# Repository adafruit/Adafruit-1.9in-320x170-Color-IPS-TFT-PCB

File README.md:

## Adafruit Adafruit 1.9" 320x170 Color IPS TFT Display - ST7789 PCB

<a href="http://www.adafruit.com/products/5394"><br/>
Click here to purchase one from the Adafruit shop</a>

PCB files for the Adafruit Adafruit 1.9" 320x170 Color IPS TFT Display - ST7789. 

Format is EagleCAD schematic and board layout
* https://www.adafruit.com/product/5394

### Description

This lovely little display breakout is the best way to add a small, colorful, and very bright display to any project. Since the display uses 4-wire SPI to communicate and has its own pixel-addressable frame buffer, it can be used with every kind of microcontroller. Even a very small one with low memory and few pins available! The 1.9" display has 320x170 16-bit full-color pixels and is an **IPS** display, so the color looks great up to 80 degrees off-axis in any direction. The TFT driver (ST7789) is very similar to the popular ST7735, and our Arduino library supports it well.

The breakout has the TFT display soldered on (it uses a delicate flex-circuit connector) as well as an ultra-low-dropout 3.3V regulator, auto-reset circuitry, and a 3/5V level shifter so you can use it with 3.3V or 5V power and logic. We also had a little extra space, so we placed a microSD card holder so you can easily load full color bitmaps from a FAT16/FAT32 formatted microSD card. The microSD card is not included, [but you can pick one up here](https://www.adafruit.com/product/5251).

Of course, we wouldn't just leave you with a datasheet and a "good luck!" - [we've written a full open-source graphics Arduino library that can draw pixels, lines, rectangles, circles, text, and bitmaps as well as example code](https://github.com/adafruit/Adafruit-ST7735-Library). The code is written for Arduino but can be easily ported to your favorite microcontroller! Wiring is easy, we strongly encourage using the hardware SPI pins of your Arduino as software SPI is noticeably slower when dealing with this size display. [For Raspberry Pi or other Single Board Computer Python users, we have a user-space Pillow-compatible library](https://github.com/adafruit/Adafruit_CircuitPython_RGB_Display). For [CircuitPython there's a displayio driver for native support](https://github.com/adafruit/Adafruit_CircuitPython_ST7789).

This display breakout also features an 18-pin "EYE SPI" standard FPC connector with flip-top connector. You can use an 18-pin 0.5mm pitch FPC cable to connect to all the GPIO pins, for when you want to skip the soldering.

**Please note!** This display is designed original for smartwatches and similar, where there's a glass over the screen. Without something gently holding the screen down, the backlight can eventually peel away from the TFT. (It's not destructive but it's unattractive) You can prevent this by, ideally, adding a plastic or glass cover/overlay. If using bare, try dabbing a touch of E6000 or similar craft glue on the thin side edges, or using a thin piece of tape to keep the front TFT attached to the backlight.

### License

Adafruit invests time and resources providing this open source design, please support Adafruit and open-source hardware by purchasing products from [Adafruit](https://www.adafruit.com)!

Designed by Limor Fried/Ladyada for Adafruit Industries.

Creative Commons Attribution/Share-Alike, all text above must be included in any redistribution. 
See license.txt for additional details.

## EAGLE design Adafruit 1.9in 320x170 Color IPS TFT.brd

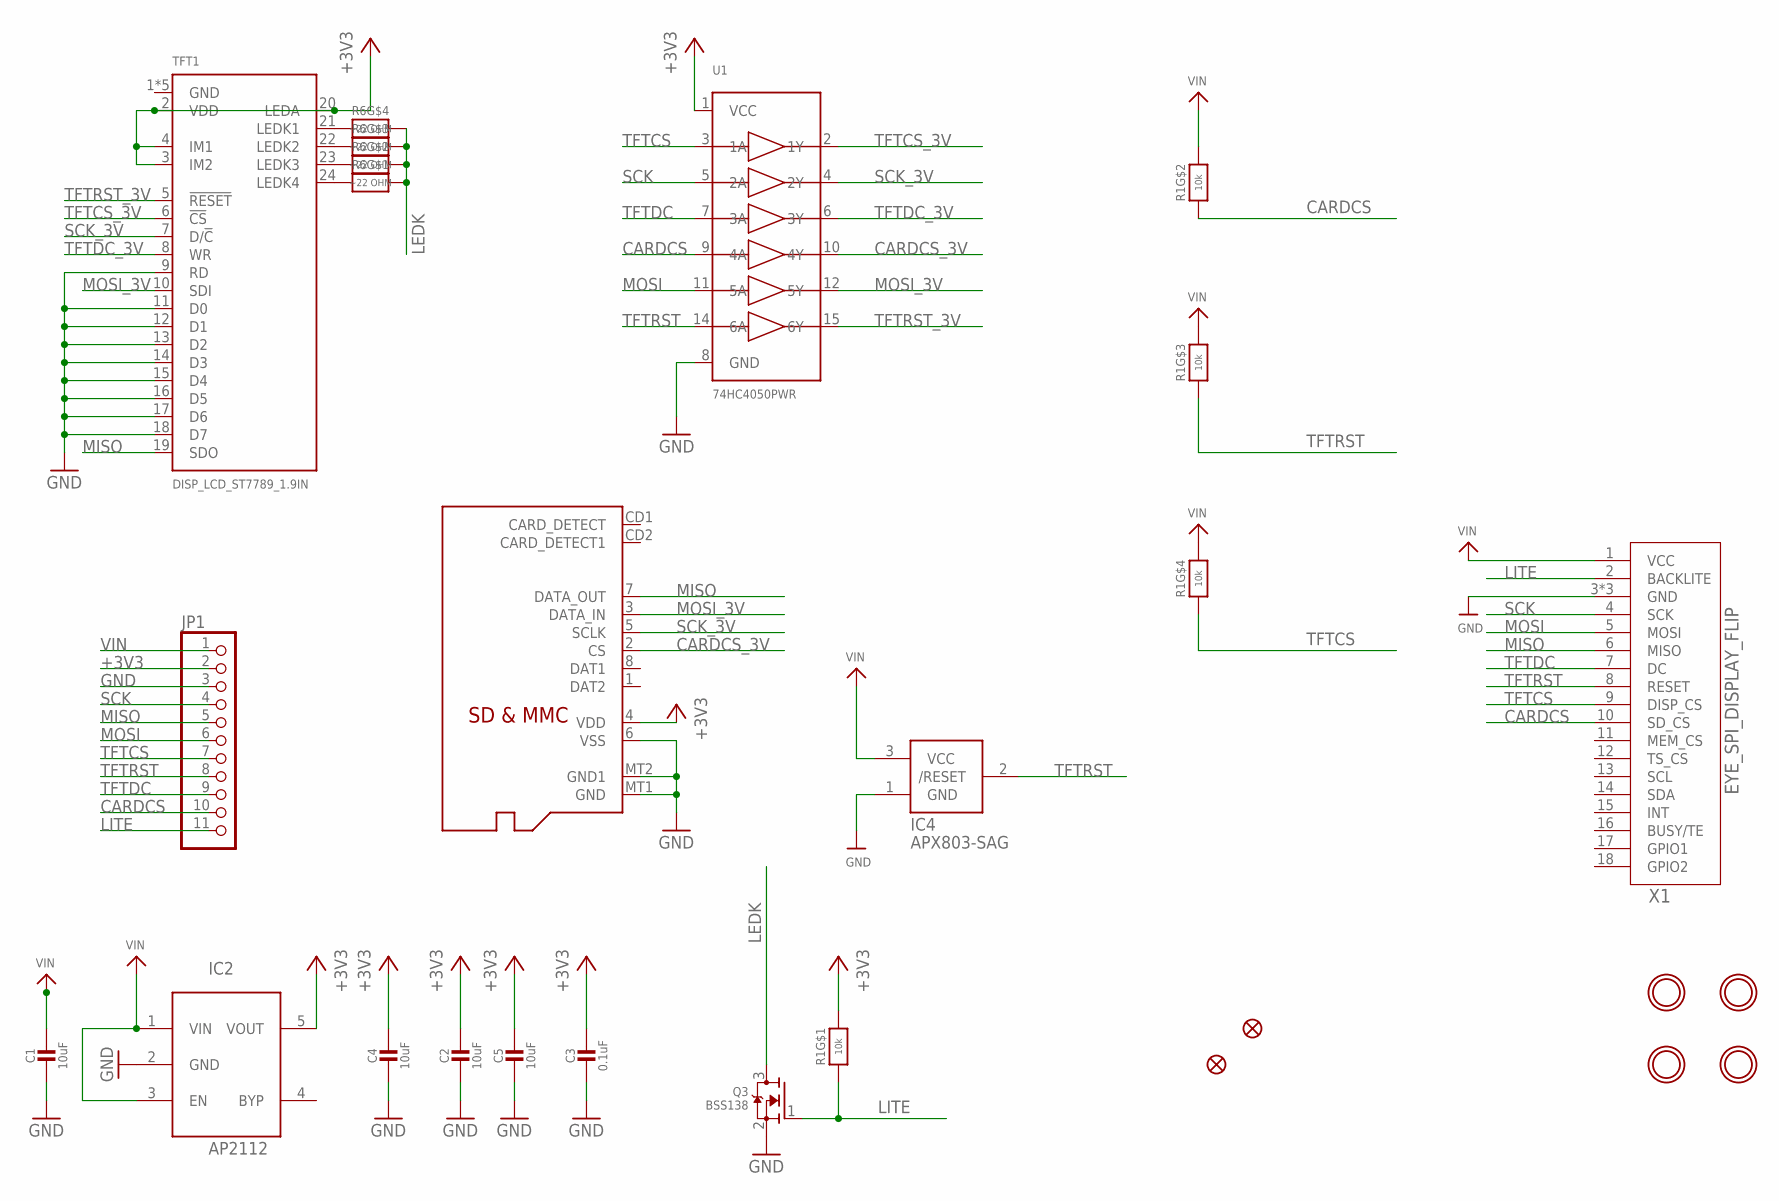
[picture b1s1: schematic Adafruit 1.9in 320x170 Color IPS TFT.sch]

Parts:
C1, C2, C4, C5: 10uF; 0805-NO
C3: 0.1uF; 0603-NO
IC2: AP2112; SOT23-5L
IC4: APX803-SAG; SOT23
JP1: HEADER-1X1176MIL; 1X11_ROUND_76
Q2: MICROSD
Q3: BSS138; SOT23-WIDE
R1: 10k; RESPACK_4X0603
R6: ~22 OHM; RESPACK_4X0603
TFT1: DISP_LCD_ST7789_1.9IN; TFT_1.9IN_170X320_30P
U1: 74HC4050PWR; TSSOP16
U$4, U$5: FIDUCIAL_1MM
U$7, U$8, U$9, U$10: MOUNTINGHOLE2.5; MOUNTINGHOLE_2.5_PLATED
X1: EYE_SPI_DISPLAY_FLIP; EYE_SPI_DISPLAY_BOTCONTACT

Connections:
+3V3: C2.1, C3.1, C4.1, C5.1, IC2.5 (VOUT), JP1.2, Q2.4 (VDD), R1.8 (2), TFT1.2 (VDD), TFT1.3 (IM2), TFT1.4 (IM1), TFT1.20 (LEDA), U1.1 (VCC)
CARDCS: JP1.10, R1.2 (1), U1.9 (4A), X1.10 (SD_CS)
CARDCS_3V: Q2.2 (CS), U1.10 (4Y)
GND: C1.2, C2.2, C3.2, C4.2, C5.2, IC2.2 (GND), IC4.1 (GND), JP1.3, Q2.6 (VSS), Q2.MT1 (GND), Q2.MT2 (GND1), Q3.2 (S), TFT1.1 (GND), TFT1.9 (RD), TFT1.11 (D0), TFT1.12 (D1), TFT1.13 (D2), TFT1.14 (D3), TFT1.15 (D4), TFT1.16 (D5), TFT1.17 (D6), TFT1.18 (D7), TFT1.25 (GND), TFT1.30 (GND), TFT1.MNT1 (GND), TFT1.MNT2 (GND), U1.8 (GND), X1.3 (GND), X1.SUPPORT1 (GND), X1.SUPPORT2 (GND)
LEDK: Q3.3 (D), R6.5 (2), R6.6 (2), R6.7 (2), R6.8 (2)
LITE: JP1.11, Q3.1 (G), R1.1, X1.2 (BACKLITE)
MISO: JP1.5, Q2.7 (DATA_OUT), TFT1.19 (SDO), X1.6 (MISO)
MOSI: JP1.6, U1.11 (5A), X1.5 (MOSI)
MOSI_3V: Q2.3 (DATA_IN), TFT1.10 (SDI), U1.12 (5Y)
unnamed: R6.4 (1), TFT1.21 (LEDK1)
unnamed: R6.3 (1), TFT1.22 (LEDK2)
unnamed: R6.2 (1), TFT1.23 (LEDK3)
unnamed: R6.1, TFT1.24 (LEDK4)
SCK: JP1.4, U1.5 (2A), X1.4 (SCK)
SCK_3V: Q2.5 (SCLK), TFT1.7 (D/!C), U1.4 (2Y)
TFTCS: JP1.7, R1.4 (1), U1.3 (1A), X1.9 (DISP_CS)
TFTCS_3V: TFT1.6 (!CS), U1.2 (1Y)
TFTDC: JP1.9, U1.7 (3A), X1.7 (DC)
TFTDC_3V: TFT1.8 (WR), U1.6 (3Y)
TFTRST: IC4.2 (/RESET), JP1.8, R1.3 (1), U1.14 (6A), X1.8 (RESET)
TFTRST_3V: TFT1.5 (!RESET), U1.15 (6Y)
VIN: C1.1, IC2.1 (VIN), IC2.3 (EN), IC4.3 (VCC), JP1.1, R1.5 (2), R1.6 (2), R1.7 (2), X1.1 (VCC)

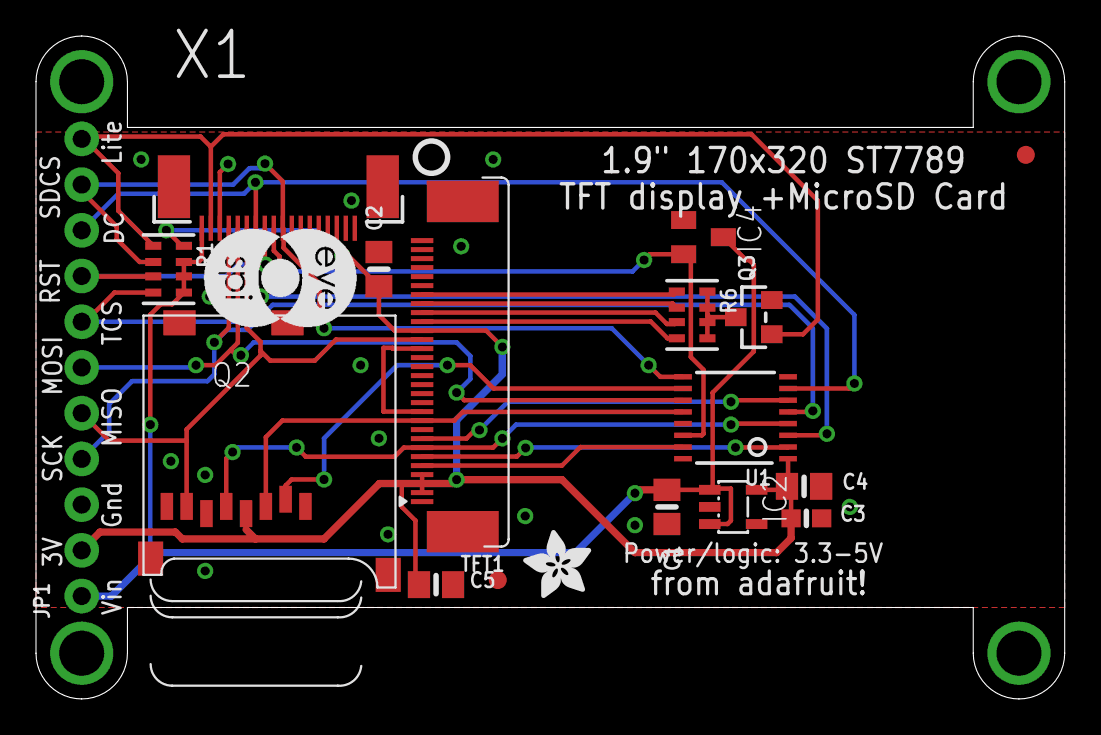
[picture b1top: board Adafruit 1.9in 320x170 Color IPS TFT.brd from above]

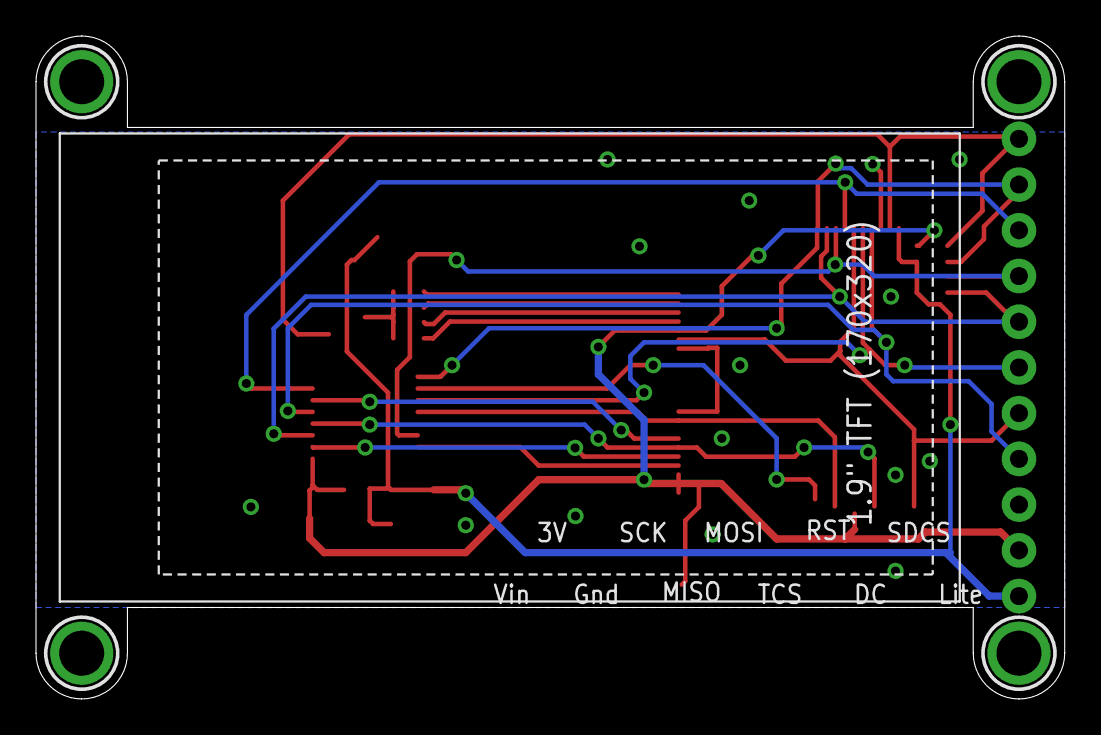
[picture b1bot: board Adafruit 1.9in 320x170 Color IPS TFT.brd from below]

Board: 2 copper layers, 57.1 x 36.8 mm, 24 parts (4 on the bottom side), 22 nets.

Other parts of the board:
U$2: PCBFEAT-REV-040
U$21: ADAFRUIT_3.5MM
U$22: EYESPI_MINI_LOGO

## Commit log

2022-03-28 Added files

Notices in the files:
parts and their libraries:
microbuilder: This work is placed in the public domain, and may be freely used for commercial and non-commercial work with the following conditions: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
